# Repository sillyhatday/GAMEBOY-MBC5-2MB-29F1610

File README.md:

# GAMEBOY-FLASHCART-MBC5-29F1610-2MB

A working PCB layout for making your own MBC5 2MB based Gameboy cartridge. I've sat on this project for years. I could not get the flash to program for a long time, so I gave up on it as it has limited use. A few years ago I got the chip to program in FlashGBX under the BungDoctor profile. In the newer versions the cartridge is correctly detected as such and should not need manually setting.

>[!NOTE]
>If the cart is not detected as writable, manually select the BungDoctor cartridge in FlashGBX

## ⚪ Game Compatibility

Nearly all Gameboy colour games used this memory mapper. It can address up to 8MB of game storage and up to 128KB of game save storage. This one only using 2MB of ROM and 32KB of RAM. 95% of GBC games using this mapper are within this range. Most 8KB save files should work fine on the 32KB chip also. 

Earlier games from the DMG should work, Nintendo kept each revision of mapper compatible with the previous (for the most part). So long as programmers followed Nintendos suggestions when developing. Mole Mania wasn't designed for an MBC5 and works perfectly, yet Zelda - Links Awakening doesn't, it crashes when saving.

>[!WARNING]
>This cart will not work properly for real time clock games. This means games like Pokemon G/S/C.

## 📷 Photos

## 🟣 Bill of materials:

>[!IMPORTANT]
>When ordering PCBs, be sure to order in 0.8mm thickness with gold plating!

| Part | Quantity |
|--------------|----|
| 29F1610 Flash | x1 |
| FM1808 or FM18W08* | x1 |
| MBC5 | x1 |
| SN74LVC1G332DBVR | x1 |
| 10K 0603 resistor | x2 |
| 0.1uF 0603 capacitor | x4 |

**FM18L08 will work but is not suggested*

### 💻 EEPROM 29F1610 <br>
I found these were really cheap as an alternative to the usual 5v chips used. They are not that available and not often that cheap, around €2 per chip. These are a 16-bit address and 8/16-bit data bus EEPROM. They can be configured to us word/byte mode. The write enable pin is brought to the audio pin on the Gameboy cartridge header. This is compatible with the GBxCart RW. The pin is held to 5v to keep it disabled during usage through a pullup resistor.

### 🐏 FRAM FM1808 <br>
These are expensive. Current prices are €11.90 from Mouser. They are available for much less on Aliexpress, for the same price you can get 5 - 10. These are known to be ***extremely*** unreliable. You are likely buying factory rejects that don't fully work or meet the speed rating. In a batch of 5 from Aliexpress I got, none of them worked. Another 10 I got, I went through 4 before finding a working one. In the end I went through 8 chips before getting one that works. The cost of 9 dodgy chips was more than one from Mouser.

### ❗OR Gate SN74LVC1G332DBVR
I consider this optional but reccomended. In my testing, I have not found that games under 2MB in size require extra glue logic. I'd still use it to be confident that your game saves will be safe.

### ❔ Memory Controller MBC5 <br>
You used to be able to go on eBay and find trash games for €3 easily, some deals I've had as low as €1. I could go on eBay and grab one or two of them per week. They seem to have gone up and the best deals are about €5 now. You'll need a hot air station to remove the chip from the board.

## Links

🏷️ NextStopPlease Labels: https://nextstopplease.square.site/ <br>
📷 NextStopPlease Insta: https://www.instagram.com/nxt.stop.please/ <br>
🛍️ Inside Gadgets Shop: https://shop.insidegadgets.com <br>
📎 Inside Gadgets GitHub: https://github.com/insidegadgets <br>
📷 Inside Gadgets Insta: https://www.instagram.com/inside.gadgets <br>
🖇️ Bytendo Mods GitHub: https://github.com/bytendomods <br>
🐭 Bucket Mouse: https://github.com/Bucket-Mouse <br>
🛒 Natalie Shop: https://nataliethenerd.com/ <br>
🤓 Natalie GitHub: https://github.com/natalie-lang/natalie <br>

## ⚖️ License

This work is licensed under a Creative Commons Attribution-ShareAlike 4.0 International License. You are able to copy and redistribute the material in any medium or format, as well as remix, transform, or build upon the material for any purpose (even commercial) - but you must give appropriate credit, provide a link to the license, and indicate if any changes were made.

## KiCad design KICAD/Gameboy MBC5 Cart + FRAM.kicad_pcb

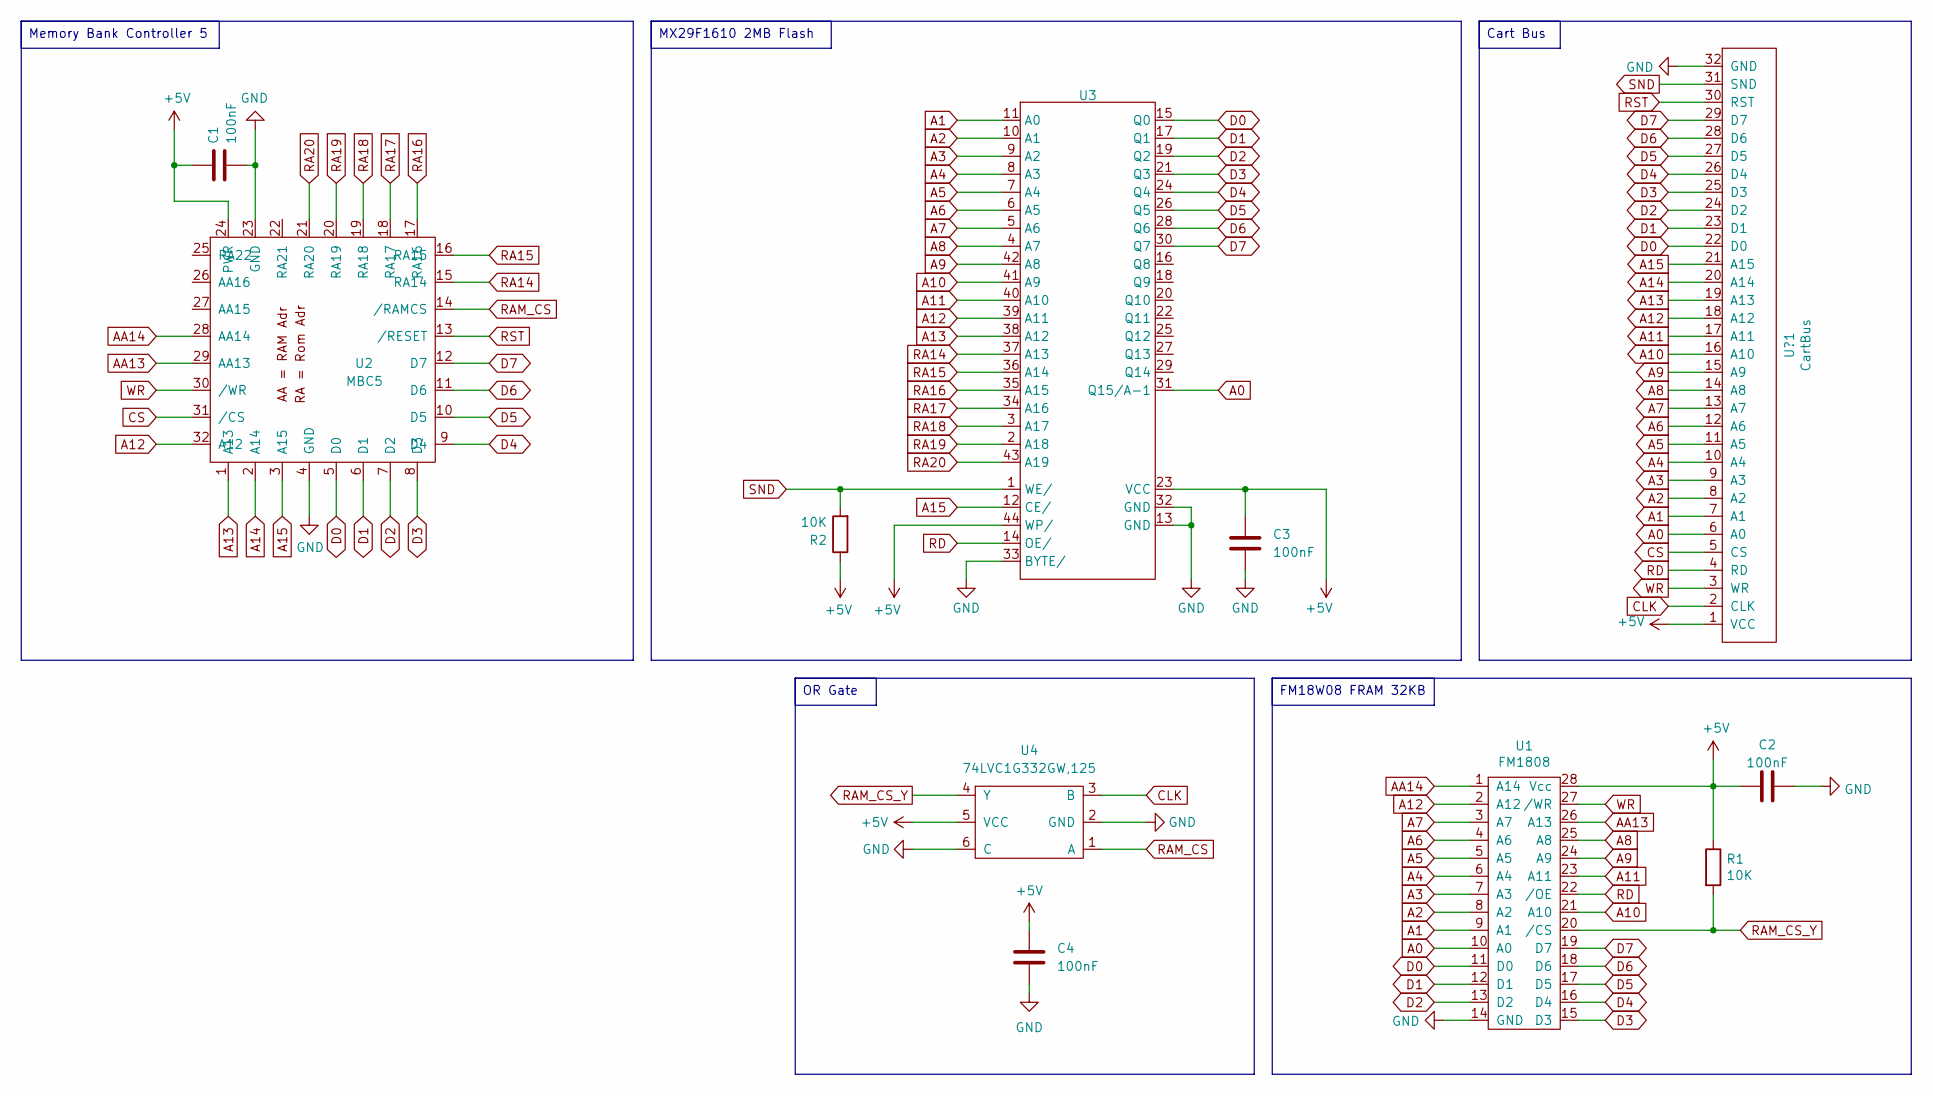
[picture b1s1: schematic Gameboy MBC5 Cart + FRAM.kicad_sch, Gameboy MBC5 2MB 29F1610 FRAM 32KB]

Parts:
C1, C2, C3, C4: 100nF; C_0603_1608Metric_Pad1.08x0.95mm_HandSolder
R1, R2: 10K; R_0603_1608Metric_Pad0.98x0.95mm_HandSolder
U1: FM1808; SOIC-28W_7.5x17.9mm_P1.27mm
U2: MBC5; LQFP-32_7x7mm_P0.8mm
U3: PSOP-44_16.9x27.17mm_P1.27mm
U4: 74LVC1G332GW,125; TSOP-6_1.65x3.05mm_P0.95mm
U?1: CartBus; GameBoy_GamePak_DMG-09_P1.50mm_Edge

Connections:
+5V: C1.1, C2.1, C3.1, C4.1, R1.1, R2.1, U1.28 (Vcc), U2.24 (PWR), U3.23 (VCC), U3.44 (WP/), U4.5 (VCC), U?1.1 (VCC)
A0: U1.10 (A0), U3.31 (Q15/A-1), U?1.6 (A0)
A1: U1.9 (A1), U3.11 (A0), U?1.7 (A1)
A2: U1.8 (A2), U3.10 (A1), U?1.8 (A2)
A3: U1.7 (A3), U3.9 (A2), U?1.9 (A3)
A4: U1.6 (A4), U3.8 (A3), U?1.10 (A4)
A5: U1.5 (A5), U3.7 (A4), U?1.11 (A5)
A6: U1.4 (A6), U3.6 (A5), U?1.12 (A6)
A7: U1.3 (A7), U3.5 (A6), U?1.13 (A7)
A8: U1.25 (A8), U3.4 (A7), U?1.14 (A8)
A9: U1.24 (A9), U3.42 (A8), U?1.15 (A9)
A10: U1.21 (A10), U3.41 (A9), U?1.16 (A10)
A11: U1.23 (A11), U3.40 (A10), U?1.17 (A11)
A12: U1.2 (A12), U2.32 (A12), U3.39 (A11), U?1.18 (A12)
A13: U2.1 (A13), U3.38 (A12), U?1.19 (A13)
A14: U2.2 (A14), U?1.20 (A14)
A15: U2.3 (A15), U3.12 (CE/), U?1.21 (A15)
AA13: U1.26 (A13), U2.29 (AA13)
AA14: U1.1 (A14), U2.28 (AA14)
CLK: U4.3 (B), U?1.2 (CLK~)
CS: U2.31 (/CS), U?1.5 (CS)
D0: U1.11 (D0), U2.5 (D0), U3.15 (Q0), U?1.22 (D0)
D1: U1.12 (D1), U2.6 (D1), U3.17 (Q1), U?1.23 (D1)
D2: U1.13 (D2), U2.7 (D2), U3.19 (Q2), U?1.24 (D2)
D3: U1.15 (D3), U2.8 (D3), U3.21 (Q3), U?1.25 (D3)
D4: U1.16 (D4), U2.9 (D4), U3.24 (Q4), U?1.26 (D4)
D5: U1.17 (D5), U2.10 (D5), U3.26 (Q5), U?1.27 (D5)
D6: U1.18 (D6), U2.11 (D6), U3.28 (Q6), U?1.28 (D6)
D7: U1.19 (D7), U2.12 (D7), U3.30 (Q7), U?1.29 (D7)
GND: C1.2, C2.2, C3.2, C4.2, U1.14 (GND), U2.4 (GND), U2.23 (GND), U3.13 (GND), U3.32 (GND), U3.33 (BYTE/), U4.2 (GND), U4.6 (C), U?1.32 (GND)
RA14: U2.15 (RA14), U3.37 (A13)
RA15: U2.16 (RA15), U3.36 (A14)
RA16: U2.17 (RA16), U3.35 (A15)
RA17: U2.18 (RA17), U3.34 (A16)
RA18: U2.19 (RA18), U3.3 (A17)
RA19: U2.20 (RA19), U3.2 (A18)
RA20: U2.21 (RA20), U3.43 (A19)
RAM_CS: U2.14 (/RAMCS), U4.1 (A)
RAM_CS_Y: R1.2, U1.20 (/CS), U4.4 (Y)
RD: U1.22 (/OE), U3.14 (OE/), U?1.4 (RD)
RST: U2.13 (/RESET), U?1.30 (RST)
SND: R2.2, U3.1 (WE/), U?1.31 (SND)
WR: U1.27 (/WR), U2.30 (/WR), U?1.3 (WR)

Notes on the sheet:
OR Gate
Cart Bus
Memory Bank Controller 5
FM18W08 FRAM 32KB
MX29F1610 2MB Flash

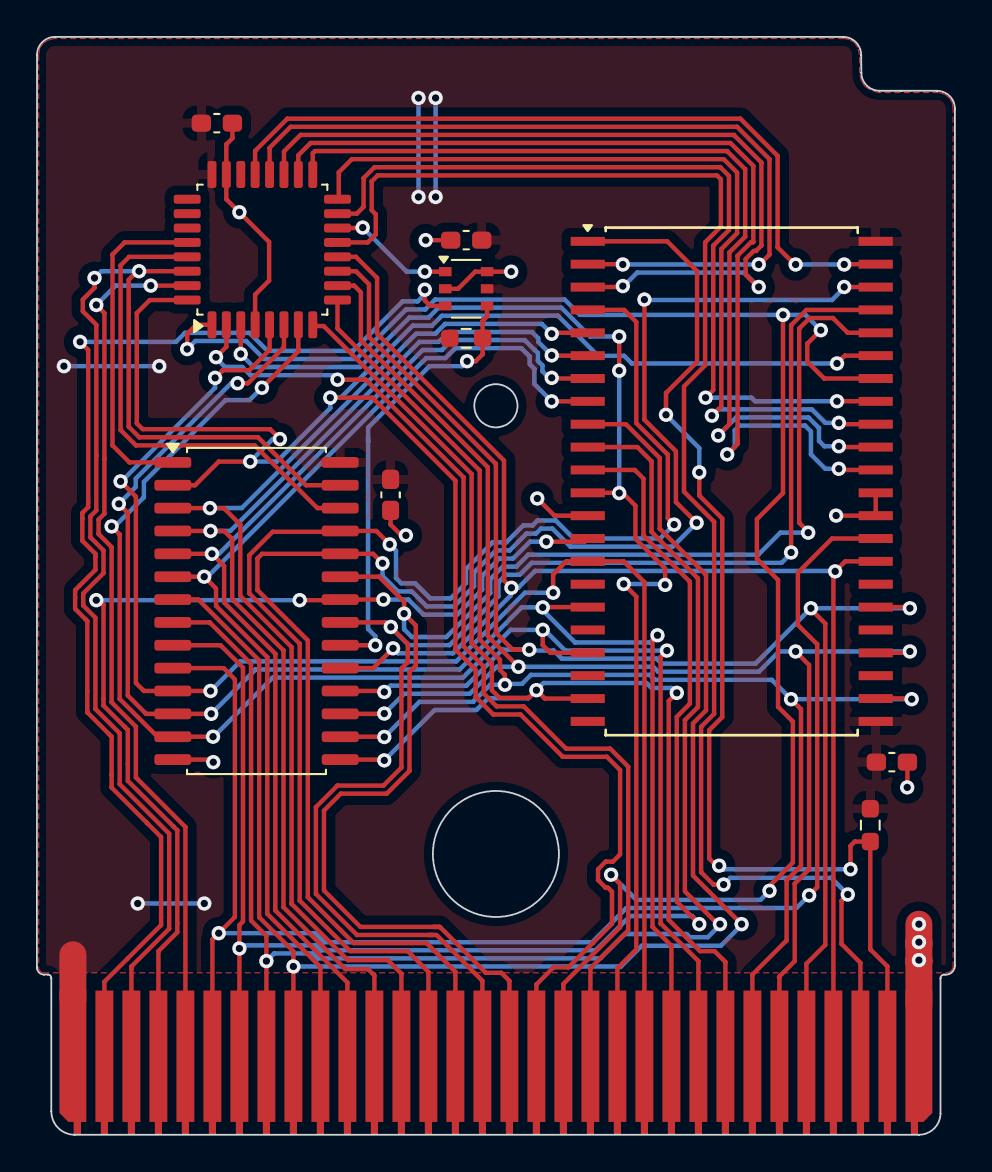
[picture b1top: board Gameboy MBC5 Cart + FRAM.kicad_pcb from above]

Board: 2 copper layers, 51.0 x 61.0 mm, 11 parts (0 on the bottom side), 43 nets.

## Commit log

2026-06-28 Create dummy
2026-06-29 Create LICENSE
